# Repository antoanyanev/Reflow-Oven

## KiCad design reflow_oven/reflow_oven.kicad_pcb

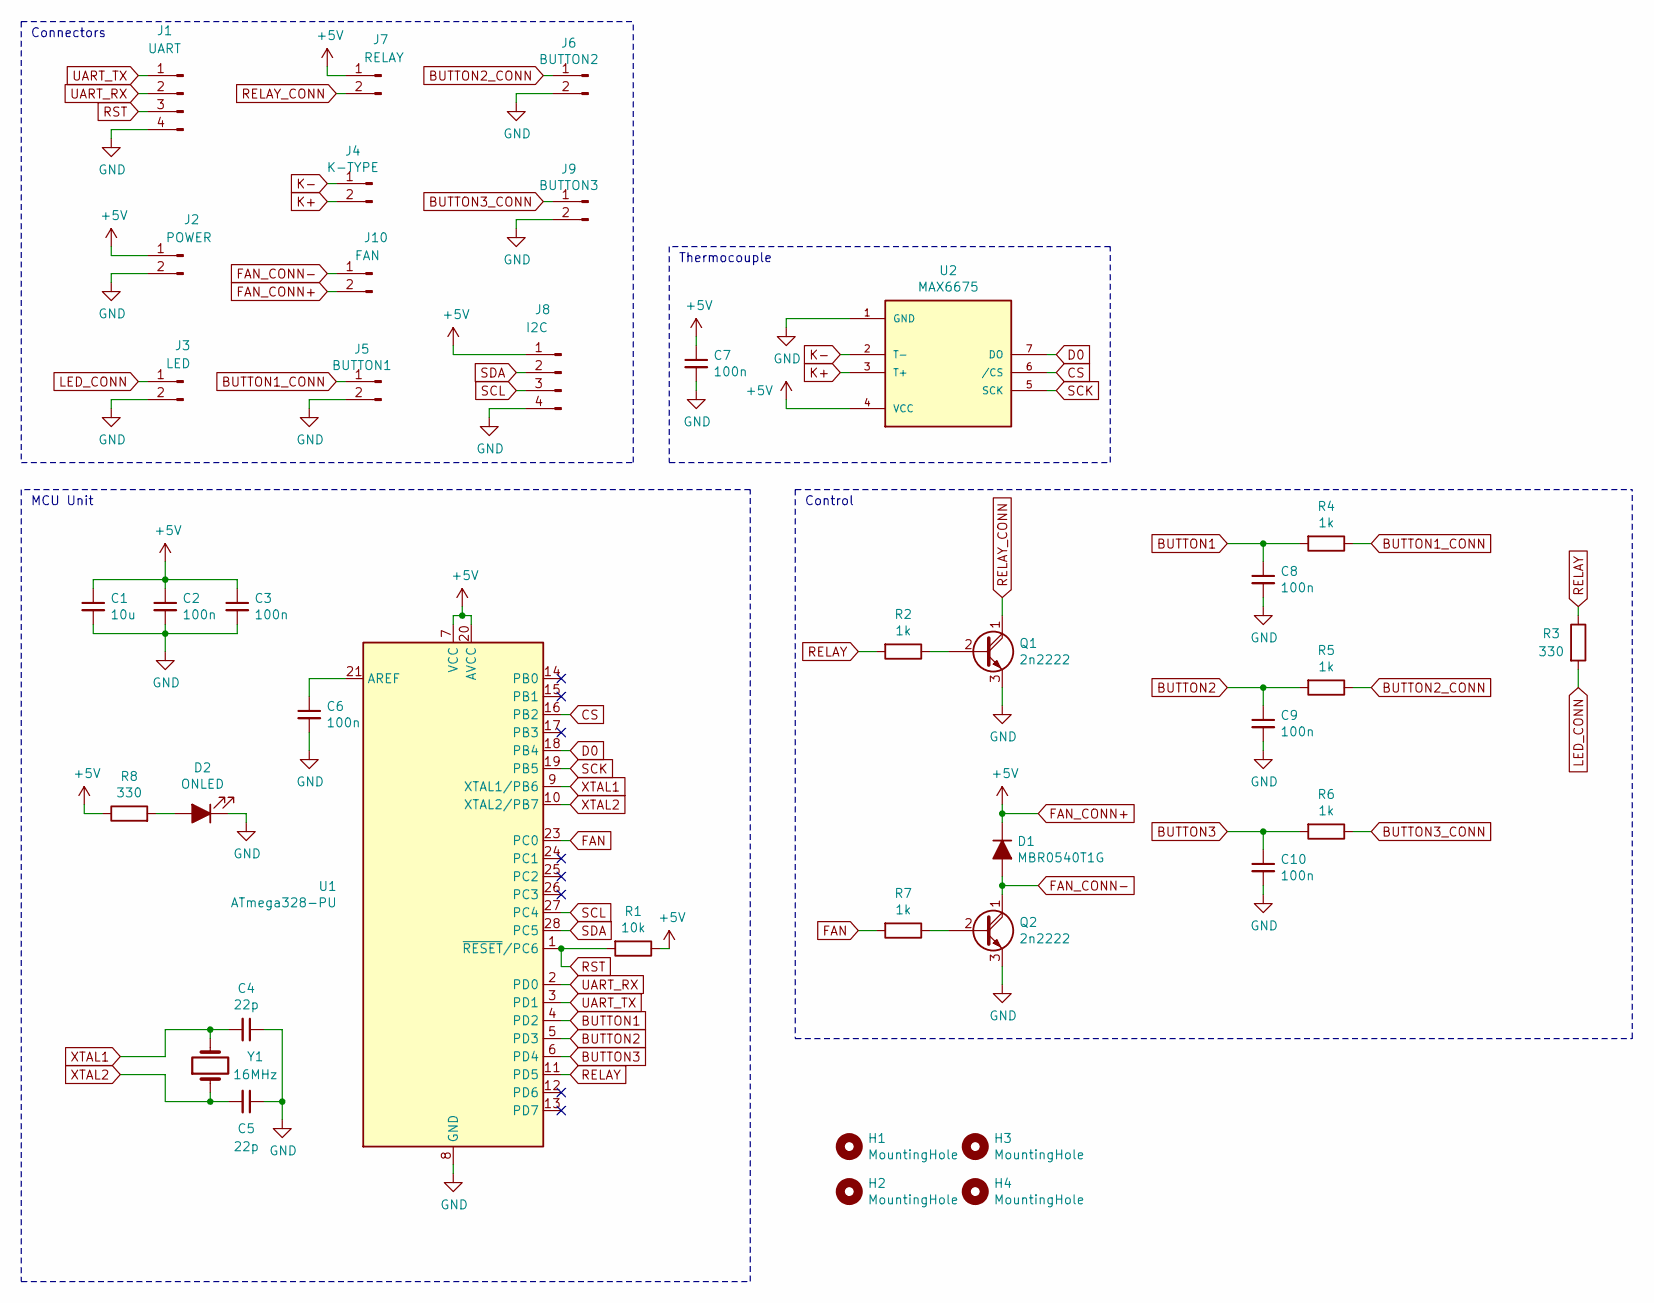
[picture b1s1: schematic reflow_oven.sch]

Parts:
C1: 10u; C_0805_2012Metric
C2, C3, C6, C7, C8, C9, C10: 100n; C_0805_2012Metric
C4, C5: 22p; C_0805_2012Metric
D1: MBR0540T1G; D_SOD-123
D2: ONLED; LED_1206_3216Metric
H1, H2, H3, H4: MountingHole; MountingHole_3mm_Pad_Via
J1: UART; Molex_KK-254_AE-6410-04A_1x04_P2.54mm_Vertical
J2: POWER; Molex_KK-254_AE-6410-02A_1x02_P2.54mm_Vertical
J3: LED; Molex_KK-254_AE-6410-02A_1x02_P2.54mm_Vertical
J4: K-TYPE; Molex_KK-254_AE-6410-02A_1x02_P2.54mm_Vertical
J5: BUTTON1; Molex_KK-254_AE-6410-02A_1x02_P2.54mm_Vertical
J6: BUTTON2; Molex_KK-254_AE-6410-02A_1x02_P2.54mm_Vertical
J7: RELAY; Molex_KK-254_AE-6410-02A_1x02_P2.54mm_Vertical
J8: I2C; Molex_KK-254_AE-6410-04A_1x04_P2.54mm_Vertical
J9: BUTTON3; Molex_KK-254_AE-6410-02A_1x02_P2.54mm_Vertical
J10: FAN; Molex_KK-254_AE-6410-02A_1x02_P2.54mm_Vertical
Q1, Q2: 2n2222; TO-92_Inline
R1: 10k; R_0805_2012Metric
R2, R4, R5, R6, R7: 1k; R_0805_2012Metric
R3, R8: 330; R_0805_2012Metric
U1: ATmega328-PU; DIP-28_W7.62mm
U2: MAX6675; SO-8_3.9x4.9mm_P1.27mm
Y1: 16MHz; Crystal_SMD_HC49-SD

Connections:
BUTTON1: C8.1, R4.2, U1.4 (PD2)
BUTTON1_CONN: J5.1, R4.1
BUTTON2: C9.1, R5.2, U1.5 (PD3)
BUTTON2_CONN: J6.1, R5.1
BUTTON3: C10.1, R6.2, U1.6 (PD4)
BUTTON3_CONN: J9.1, R6.1
CS: U1.16 (PB2), U2.6 (/CS)
D0: U1.18 (PB4), U2.7 (DO)
FAN: R7.2, U1.23 (PC0)
FAN_CONN+: C1.1, C2.1, C3.1, C7.1, D1.1 (K), J2.1, J7.1, J8.1, J10.2, R1.1, R8.1, U1.7 (VCC), U1.20 (AVCC), U2.4 (VCC)
FAN_CONN-: D1.2 (A), J10.1, Q2.1 (C)
GND: C1.2, C2.2, C3.2, C4.1, C5.1, C6.2, C7.2, C8.2, C9.2, C10.2, D2.1 (K), J1.4, J2.2, J3.2, J5.2, J6.2, J8.4, J9.2, Q1.3 (E), Q2.3 (E), U1.8 (GND), U1.22 (GND), U2.1 (GND)
K+: J4.2, U2.3 (T+)
K-: J4.1, U2.2 (T-)
LED_CONN: J3.1, R3.2
unnamed: C6.1, U1.21 (AREF)
unnamed: D2.2 (A), R8.2
unnamed: Q1.2 (B), R2.1
unnamed: Q2.2 (B), R7.1
RELAY: R2.2, R3.1, U1.11 (PD5)
RELAY_CONN: J7.2, Q1.1 (C)
RST: J1.3, R1.2, U1.1 (~RESET~/PC6)
SCK: U1.19 (PB5), U2.5 (SCK)
SCL: J8.3, U1.27 (PC4)
SDA: J8.2, U1.28 (PC5)
UART_RX: J1.2, U1.2 (PD0)
UART_TX: J1.1, U1.3 (PD1)
XTAL1: C4.2, U1.9 (XTAL1/PB6), Y1.2
XTAL2: C5.2, U1.10 (XTAL2/PB7), Y1.1

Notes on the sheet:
MCU Unit
Thermocouple
Control
Connectors

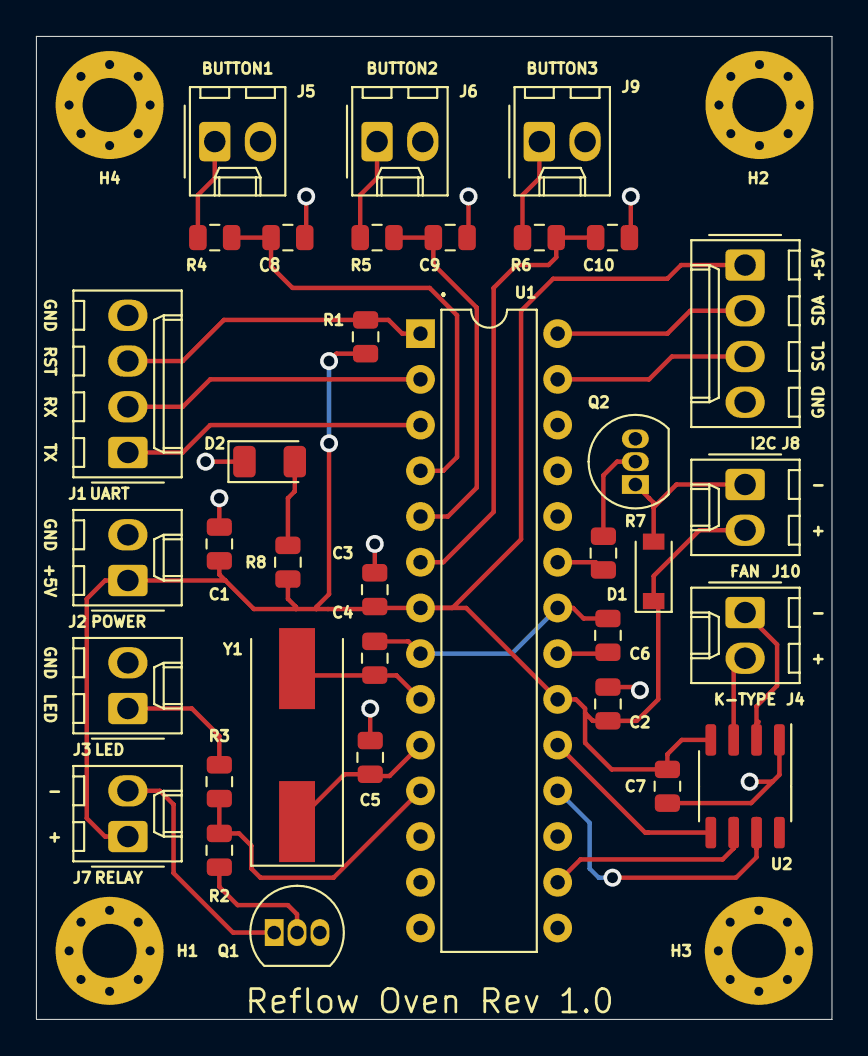
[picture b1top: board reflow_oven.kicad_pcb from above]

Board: 2 copper layers, 44.2 x 54.6 mm, 39 parts (0 on the bottom side), 29 nets.

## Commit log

2021-03-25 Added PCB
2021-03-25 Added Sketch File
2021-03-26 Updated Design
2021-03-26 Added SMD Crystal
2021-03-31 Fina ldesign
2021-04-28 Improvements
